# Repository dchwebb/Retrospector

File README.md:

# Retrospector

Retrospector is a Eurorack format stereo digital delay. 

Delay times can be set clocked or free-running and left and right channels can be independent or the right channel set as a multiple of the left channel. The delay times are switchable between short, long and reversed with maximum delay times over 5 minutes.

The feedback path can be filtered with settings allowing a sweep from low pass to high pass, or either separately. The delayed signal can be modulated for subtle chorussing effects or left and right channels fed back into each other to widen dual mono sources.

The feedback control allows greater than 100% regeneration allowing the delay to increase the volume of the delayed signal.

Three RGB LEDs display the delay times (using different colours to indicate clocking and channel linking) and the filter status (white to red with increasing low pass filtering and white to blue for high pass).

A USB port is available on the rear of the module providing configuration, debug and upgrade options via a serial interface.

# Technical
The module is constructed from a sandwich of three PCBs. The front panel is held to the control PCB using the potentiometers and jack sockets with light guides directing the RGB LEDs from the control PCB. The control PCB also houses the LED driver. All other components are on the component PCB and this is attached to the control PCB with standard 2.54mm headers. The component board is a 4 layer PCB; the others have 2 layers.

Retrospector is built around an STM32H743 microcontroller clocked at 400MHz. The MCU uses a pair of multi-channel 16-bit ADCs to digitise the stereo audio input signal and the various potentiometer and control voltage inputs.

The MCU controls the external DAC with I2S at 16 bits. The MCU's internal 12-bit DACs are used to control the linear VCA that carries out stereo mixing of the digital wet signal and analog dry signal.

Delay samples are held in external 32MB SDRAM controlled by the MCU's FMC peripheral. The MCU's internal memory is mainly used for DMA buffers and FIR filter buffers (better performance than the slower external RAM). The MCU also has both data and instruction caches which are used to greatly improve performance.

The three RGB LEDs are controlled by a Toshiba 9 channel LED driver (TB62781FNG) with the MCU setting colour and brightness over SPI and DMA.

The MCU also supports a USB micro-B port to allow upgrades, configuration and debugging via a serial console:

Annotated component PCB
-----------------------

A) A switched-mode power supply (Texas Instruments LM2675) converts the 12V rail to 5V which is then converted to 3.3V using an LDO. THe 5V rail also powers the RGB LEDs.

B) The mix control uses a 4 channel linear VCA (Alfa AS3364D) to control the Wet/Dry mix. This keeps the dry signal analog throughout.

C) The Output signals are mixed and inverted (to preserve signal polarity) with a TL074 and a TL072 op-amp.

D) The digital Wet signal is converted to analog using a Texas Instruments PCM5100 DAC.

E) The analog input signals (audio and control voltage) are scaled and mixed using a pair of MCP6004 op-amps.

F) The microcontroller is an STM32H743 running at 400MHz.

G) The delay beffers are stored in an external 32MB RAM module (ISSI IS42S16160J) allowing for over 5 minutes of stereo delay.

Errata
------
There were two errors on v2 hardware:

1. OpAmp U3 pin 2 and 3 incorrectly swapped. Bodge is to ground pin 3 of U3, remove capacitor C34, lift U3 pin 2 and connect it with a bodge wire to pad 2 of R24.
2. DRAM address line 12 was not connected. Bodge is to connect DRAM Pin 36 to MCU Pin 87.
3. Swapped C54 (tantalum 22uF) for ceramic 47uF (1206 25V X5R).

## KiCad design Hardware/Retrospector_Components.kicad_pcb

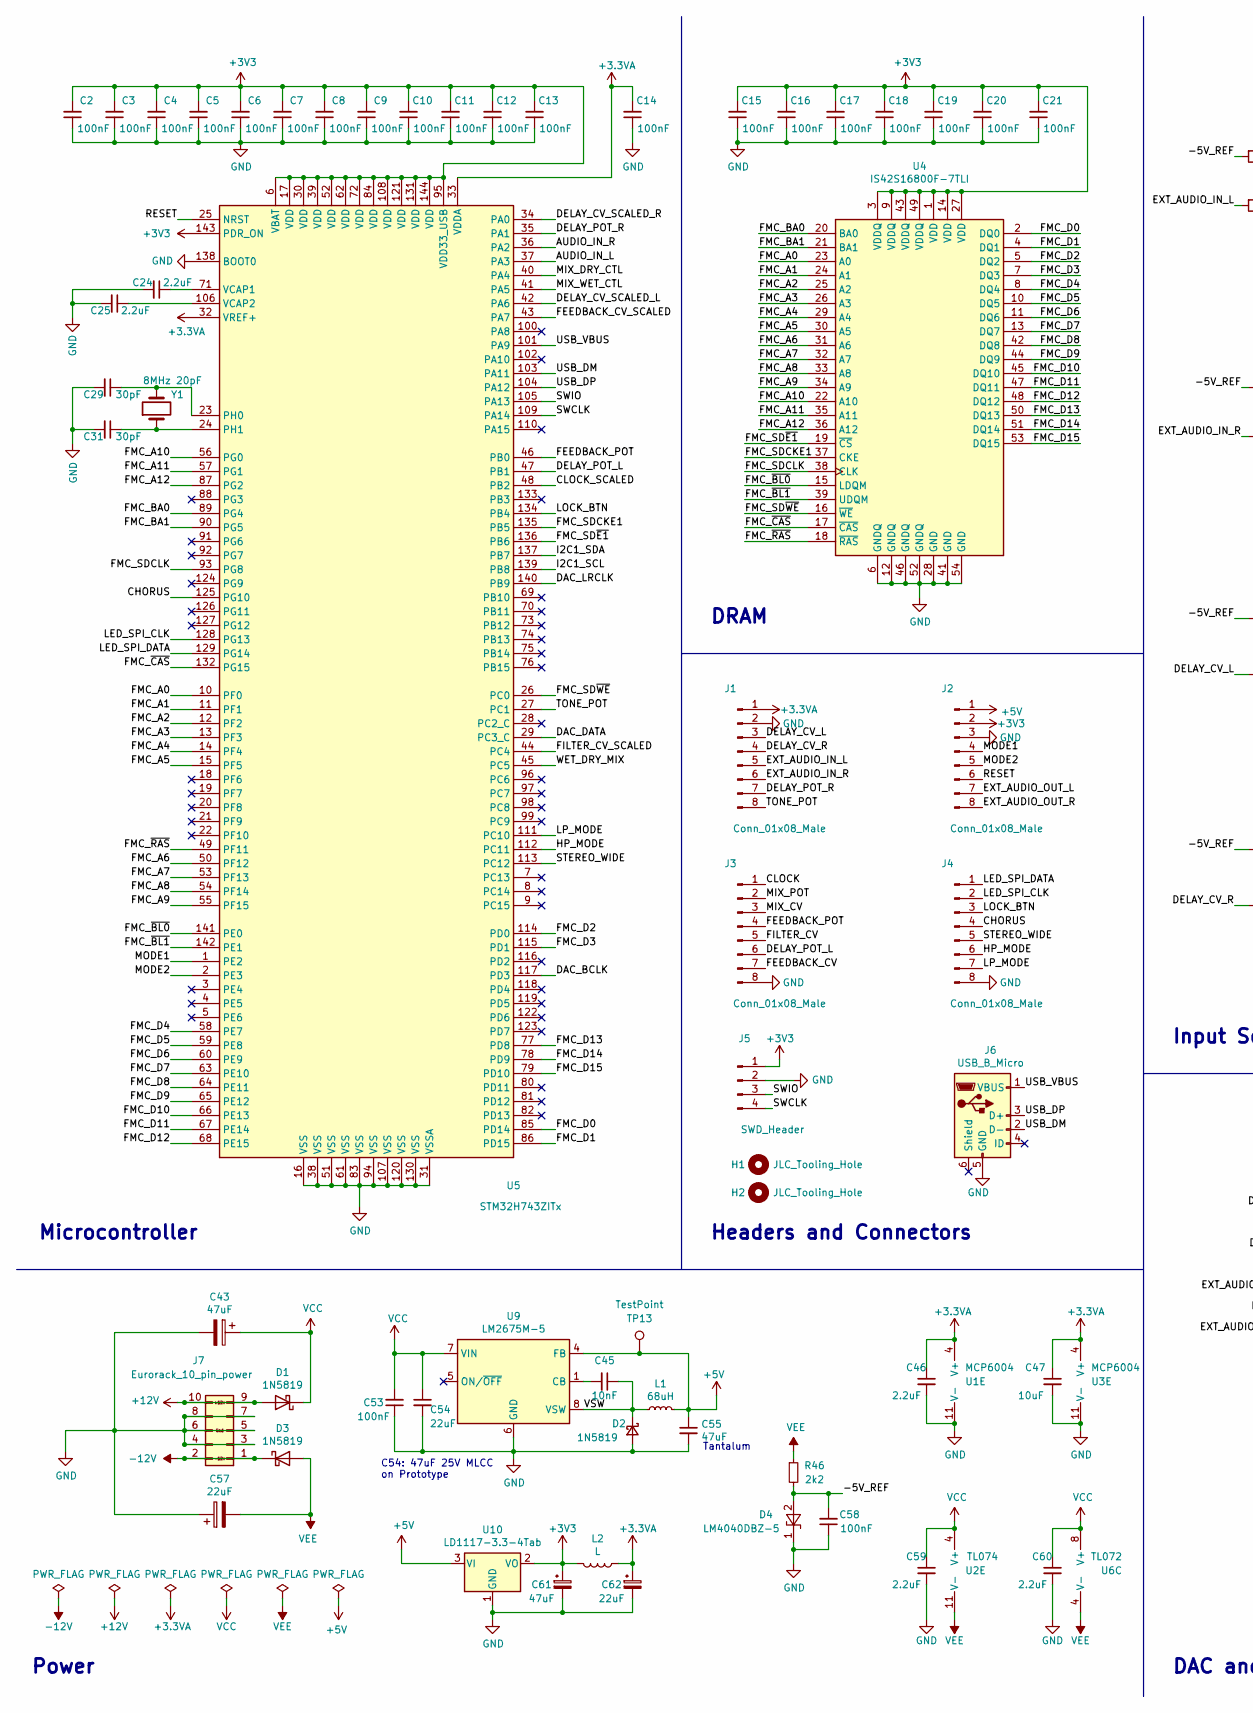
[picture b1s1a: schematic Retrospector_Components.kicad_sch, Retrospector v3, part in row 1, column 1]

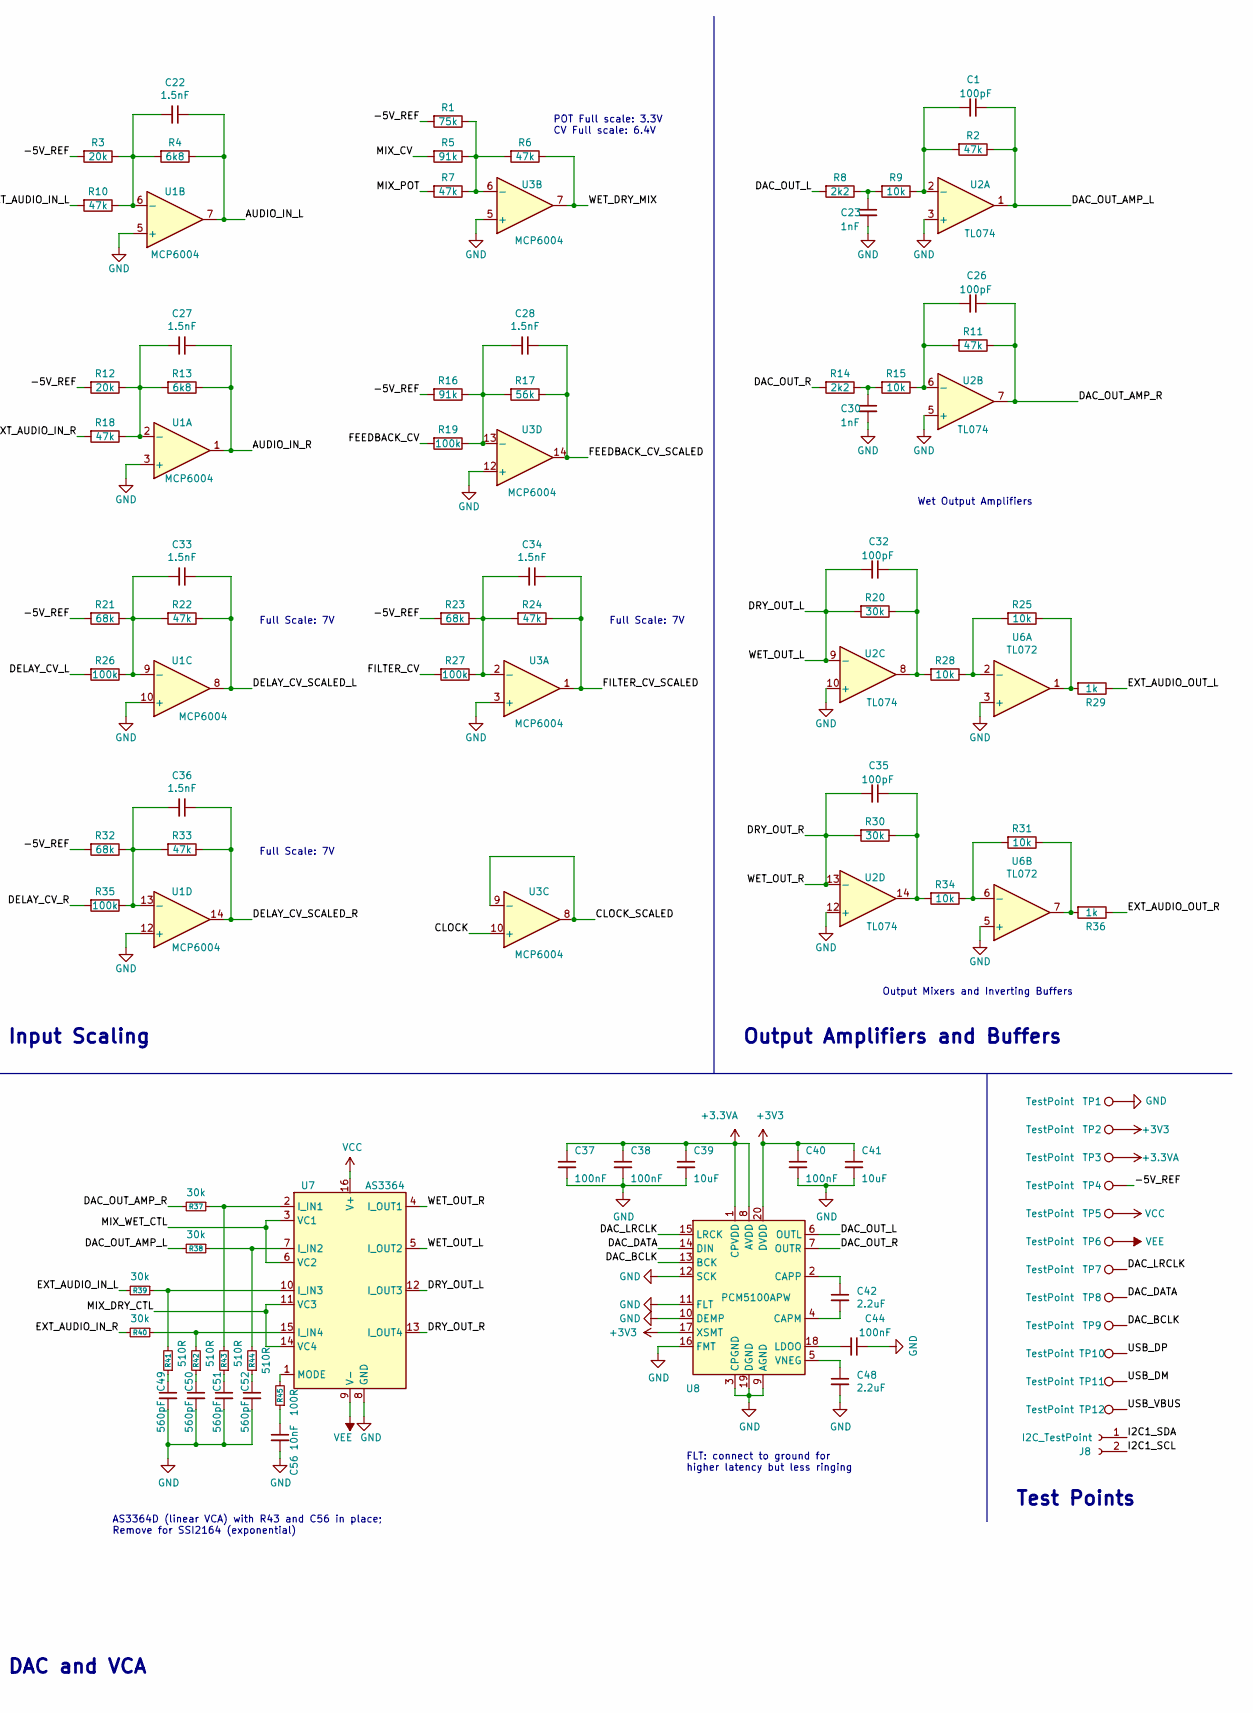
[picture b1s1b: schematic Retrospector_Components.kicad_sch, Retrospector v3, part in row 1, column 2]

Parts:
C1, C26, C32, C35: 100pF; C_0603_HandSoldering; Part_Number C14858
C2, C3, C4, C5, C6, C7, C8, C9, C10, C11, C12, C13, C14, C15, C16, C17, C18, C19, C20, C21, C37, C38, C40, C44, C58: 100nF; C_0603_HandSoldering; Part_Number C14663
C22, C27, C28, C33, C34, C36: 1.5nF; C_0603_HandSoldering; Part_Number C1595
C23, C30: 1nF; C_0603_HandSoldering; Part_Number C1588
C24, C25, C42, C46, C48, C59, C60: 2.2uF; C_0603_HandSoldering; Part_Number C23630
C29, C31: 30pF; C_0603_HandSoldering; Part_Number C22397
C39, C41, C47: 10uF; C_0805; Part_Number C15850
C43, C61: 47uF; CP_Elec_5x5.8; Part_Number C134798
C45, C56: 10nF; C_0603_HandSoldering; Part_Number C57112
C49, C50, C51, C52: 560pF; C_0603_HandSoldering; Part_Number C84721
C53: 100nF; C_0603_HandSoldering
C54: 22uF; C_1210
C55: 47uF; C_1210
C57, C62: 22uF; CP_Elec_4x5.8; Part_Number C134793
D1, D2, D3: 1N5819; D_SOD-123; Part_Number C8598
D4: LM4040DBZ-5; SOT-23; Part_Number C156291
H1, H2: JLC_Tooling_Hole; JLC_SMT_Tooling_Hole
J1, J2, J3, J4: Conn_01x08_Male; Pin_Header_Straight_1x08_Pitch2.54mm
J5: SWD_Header; SWD_header
J6: USB_B_Micro; USB_Micro-B_Amphenol
J7: Eurorack_10_pin_power; Eurorack_10_pin_header
J8: I2C_TestPoint; Pin_Header_Straight_1x02_Pitch2.54mm
L1: 68uH; TDK_Inductor_6.9x7.2
L2: L; L_0805_HandSoldering; Part_Number C1046
R1: 75k; R_0603_HandSoldering; Part_Number C23242
R2, R6, R7, R10, R11, R18, R22, R24, R33: 47k; R_0603_HandSoldering; Part_Number C25819
R3, R12: 20k; R_0603_HandSoldering; Part_Number C4184
R4, R13: 6k8; R_0603_HandSoldering; Part_Number C23212
R5, R16: 91k; R_0603_HandSoldering; Part_Number C23265
R8, R14, R46: 2k2; R_0603_HandSoldering; Part_Number C4190
R9, R15, R25, R28, R31, R34: 10k; R_0603_HandSoldering; Part_Number C25804
R17: 56k; R_0603_HandSoldering; Part_Number C23206
R19, R26, R27, R35: 100k; R_0603_HandSoldering; Part_Number C25803
R20, R30, R37, R38, R39, R40: 30k; R_0603_HandSoldering; Part_Number C22984
R21, R23, R32: 68k; R_0603_HandSoldering; Part_Number C23231
R29, R36: 1k; R_0603_HandSoldering; Part_Number C21190
R41, R42, R43, R44: 510R; R_0603_HandSoldering; Part_Number C23193
R45: 100R; R_0603_HandSoldering; Part_Number C22775
TP1, TP2, TP3, TP4, TP5, TP6: TestPoint; 1.3mm_Test_Point
TP7, TP8, TP9, TP10, TP11, TP12, TP13: TestPoint; Measurement_Point_Square-SMD-Pad_Small
U1, U3: MCP6004; SOIC-14_N; Part_Number C116668
U2: TL074; SOIC-14_N; Part_Number C6964
U4: IS42S16800F-7TLI; TSOP-II-54_22.2x10.16mm_P0.8mm; Part_Number C91278
U5: STM32H743ZITx; LQFP-144_20x20mm_P0.5mm; Part_Number C114408
U6: TL072; SOIC-8_3.9x4.9mm_Pitch1.27mm; Part_Number C6961
U7: AS3364; SOIC-16_3.9x9.9mm_Pitch1.27mm
U8: PCM5100APW; SSOP-20_4.4x6.5mm_Pitch0.65mm_Round_Pads; Part_Number C131154
U9: LM2675M-5; SOIC-8_3.9x4.9mm_Pitch1.27mm; Part_Number C180371
U10: LD1117-3.3-4Tab; SOT-223-3_TabPin2
Y1: 8MHz 20pF; Crystal_SMD_5032-2pin_5.0x3.2mm_HandSoldering; Part_Number C115962

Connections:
+3.3VA: C14.2, C37.1, C38.1, C39.1, C46.1, C47.1, C62.1, J1.1, L2.1, TP3.1, U1.4 (V+), U3.4 (V+), U5.32 (VREF+), U5.33 (VDDA), U8.1 (CPVDD), U8.8 (AVDD)
+3V3: C2.2, C3.2, C4.2, C5.2, C6.2, C7.2, C8.2, C9.2, C10.2, C11.2, C12.2, C13.2, C15.2, C16.2, C17.2, C18.2, C19.2, C20.2, C21.2, C40.1, C41.1, C61.1, J2.2, J5.1, L2.2, TP2.1, U4.1 (VDD), U4.3 (VDDQ), U4.9 (VDDQ), U4.14 (VDD), U4.27 (VDD), U4.43 (VDDQ), U4.49 (VDDQ), U5.6 (VBAT), U5.17 (VDD), U5.30 (VDD), U5.39 (VDD), U5.52 (VDD), U5.62 (VDD), U5.72 (VDD), U5.84 (VDD), U5.95 (VDD33_USB), U5.108 (VDD), U5.121 (VDD), U5.131 (VDD), U5.143 (PDR_ON), U5.144 (VDD), U8.17 (XSMT), U8.20 (DVDD), U10.2 (VO)
+5V: C55.1, J2.1, L1.2, TP13.1, U9.4 (FB), U10.3 (VI)
+12V: D1.2 (A), J7.9, J7.10
-12V: D3.1 (K), J7.1, J7.2
/-5V_REF: C58.2, D4.2 (A), R1.2, R3.2, R12.2, R16.2, R21.2, R23.2, R32.2, R46.2, TP4.1
/AUDIO_IN_L: C22.1, R4.1, U1.7, U5.37 (PA3)
/AUDIO_IN_R: C27.1, R13.1, U1.1, U5.36 (PA2)
/CHORUS: J4.4, U5.125 (PG10)
/CLOCK: J3.1, U3.10 (+)
/CLOCK_SCALED: U3.8, U3.9 (-), U5.48 (PB2)
/DAC_BCLK: TP9.1, U5.117 (PD3), U8.13 (BCK)
/DAC_DATA: TP8.1, U5.29 (PC3_C), U8.14 (DIN)
/DAC_LRCLK: TP7.1, U5.140 (PB9), U8.15 (LRCK)
/DAC_OUT_AMP_L: C1.1, R2.1, R38.2, U2.1
/DAC_OUT_AMP_R: C26.1, R11.1, R37.2, U2.7
/DAC_OUT_L: R8.2, U8.6 (OUTL)
/DAC_OUT_R: R14.2, U8.7 (OUTR)
/DELAY_CV_L: J1.3, R26.2
/DELAY_CV_R: J1.4, R35.2
/DELAY_CV_SCALED_L: C33.1, R22.1, U1.8, U5.42 (PA6)
/DELAY_CV_SCALED_R: C36.1, R33.1, U1.14, U5.34 (PA0)
/DELAY_POT_L: J3.6, U5.47 (PB1)
/DELAY_POT_R: J1.7, U5.35 (PA1)
/DRY_OUT_L: C32.2, R20.2, U2.9 (-), U7.5 (I_OUT2), U7.12 (I_OUT3)
/DRY_OUT_R: C35.2, R30.2, U2.13 (-), U7.4 (I_OUT1), U7.13 (I_OUT4)
/EXT_AUDIO_IN_L: J1.5, R10.2, R39.2
/EXT_AUDIO_IN_R: J1.6, R18.2, R40.2
/EXT_AUDIO_OUT_L: J2.7, R29.1
/EXT_AUDIO_OUT_R: J2.8, R36.1
/FEEDBACK_CV: J3.7, R19.2
/FEEDBACK_CV_SCALED: C28.1, R17.1, U3.14, U5.43 (PA7)
/FEEDBACK_POT: J3.4, U5.46 (PB0)
/FILTER_CV: J3.5, R27.2
/FILTER_CV_SCALED: C34.1, R24.1, U3.1, U5.44 (PC4)
/FMC_A0: U4.23 (A0), U5.10 (PF0)
/FMC_A1: U4.24 (A1), U5.11 (PF1)
/FMC_A2: U4.25 (A2), U5.12 (PF2)
/FMC_A3: U4.26 (A3), U5.13 (PF3)
/FMC_A4: U4.29 (A4), U5.14 (PF4)
/FMC_A5: U4.30 (A5), U5.15 (PF5)
/FMC_A6: U4.31 (A6), U5.50 (PF12)
/FMC_A7: U4.32 (A7), U5.53 (PF13)
/FMC_A8: U4.33 (A8), U5.54 (PF14)
/FMC_A9: U4.34 (A9), U5.55 (PF15)
/FMC_A10: U4.22 (A10), U5.56 (PG0)
/FMC_A11: U4.35 (A11), U5.57 (PG1)
/FMC_A12: U4.36 (A12), U5.87 (PG2)
/FMC_BA0: U4.20 (BA0), U5.89 (PG4)
/FMC_BA1: U4.21 (BA1), U5.90 (PG5)
/FMC_D0: U4.2 (DQ0), U5.85 (PD14)
/FMC_D1: U4.4 (DQ1), U5.86 (PD15)
/FMC_D2: U4.5 (DQ2), U5.114 (PD0)
/FMC_D3: U4.7 (DQ3), U5.115 (PD1)
/FMC_D4: U4.8 (DQ4), U5.58 (PE7)
/FMC_D5: U4.10 (DQ5), U5.59 (PE8)
/FMC_D6: U4.11 (DQ6), U5.60 (PE9)
/FMC_D7: U4.13 (DQ7), U5.63 (PE10)
/FMC_D8: U4.42 (DQ8), U5.64 (PE11)
/FMC_D9: U4.44 (DQ9), U5.65 (PE12)
/FMC_D10: U4.45 (DQ10), U5.66 (PE13)
/FMC_D11: U4.47 (DQ11), U5.67 (PE14)
/FMC_D12: U4.48 (DQ12), U5.68 (PE15)
/FMC_D13: U4.50 (DQ13), U5.77 (PD8)
/FMC_D14: U4.51 (DQ14), U5.78 (PD9)
/FMC_D15: U4.53 (DQ15), U5.79 (PD10)
/FMC_SDCKE1: U4.37 (CKE), U5.135 (PB5)
/FMC_SDCLK: U4.38 (CLK), U5.93 (PG8)
/FMC_SD~E1: U4.19 (~CS), U5.136 (PB6)
/FMC_SD~WE: U4.16 (~WE), U5.26 (PC0)
/FMC_~BL0: U4.15 (LDQM), U5.141 (PE0)
/FMC_~BL1: U4.39 (UDQM), U5.142 (PE1)
/FMC_~CAS: U4.17 (~CAS), U5.132 (PG15)
/FMC_~RAS: U4.18 (~RAS), U5.49 (PF11)
/HP_MODE: J4.6, U5.112 (PC11)
/I2C1_SCL: J8.2, U5.139 (PB8)
/I2C1_SDA: J8.1, U5.137 (PB7)
/LED_SPI_CLK: J4.2, U5.128 (PG13)
/LED_SPI_DATA: J4.1, U5.129 (PG14)
/LOCK_BTN: J4.3, U5.134 (PB4)
/LP_MODE: J4.7, U5.111 (PC10)
/MIX_CV: J3.3, R5.2
/MIX_DRY_CTL: U5.40 (PA4), U7.11 (VC3), U7.14 (VC4)
/MIX_POT: J3.2, R7.2
/MIX_WET_CTL: U5.41 (PA5), U7.3 (VC1), U7.6 (VC2)
/MODE1: J2.4, U5.1 (PE2)
/MODE2: J2.5, U5.2 (PE3)
/RESET: J2.6, U5.25 (NRST)
/STEREO_WIDE: J4.5, U5.113 (PC12)
/SWCLK: J5.4, U5.109 (PA14)
/SWIO: J5.3, U5.105 (PA13)
/TONE_POT: J1.8, U5.27 (PC1)
/USB_DM: J6.2 (D-), TP11.1, U5.103 (PA11)
/USB_DP: J6.3 (D+), TP10.1, U5.104 (PA12)
/USB_VBUS: J6.1 (VBUS), TP12.1, U5.101 (PA9)
/VSW: C45.1, D2.1 (K), L1.1, U9.8 (VSW)
/WET_DRY_MIX: R6.1, U3.7, U5.45 (PC5)
GND: C2.1, C3.1, C4.1, C5.1, C6.1, C7.1, C8.1, C9.1, C10.1, C11.1, C12.1, C13.1, C14.1, C15.1, C16.1, C17.1, C18.1, C19.1, C20.1, C21.1, C23.2, C24.2, C25.2, C29.2, C30.2, C31.2, C37.2, C38.2, C39.2, C40.2, C41.2, C43.2, C44.1, C46.2, C47.2, C48.2, C49.2, C50.2, C51.2, C52.2, C53.1, C54.2, C55.2, C56.2, C57.1, C58.1, C59.2, C60.2, C61.2, C62.2, D2.2 (A), D4.1 (K), J1.2, J2.3, J3.8, J4.8, J5.2, J6.5 (GND), J7.3, J7.4, J7.5, J7.6, J7.7, J7.8, TP1.1, U1.3 (+), U1.5 (+), U1.10 (+), U1.11 (V-), U1.12 (+), U2.3 (+), U2.5 (+), U2.10 (+), U2.12 (+), U3.3 (+), U3.5 (+), U3.11 (V-), U3.12 (+), U4.6 (GNDQ), U4.12 (GNDQ), U4.28 (GND), U4.41 (GND), U4.46 (GNDQ), U4.52 (GNDQ), U4.54 (GND), U5.16 (VSS), U5.31 (VSSA), U5.38 (VSS), U5.51 (VSS), U5.61 (VSS), U5.83 (VSS), U5.94 (VSS), U5.107 (VSS), U5.120 (VSS), U5.130 (VSS), U5.138 (BOOT0), U6.3 (+), U6.5 (+), U7.8 (GND), U8.3 (CPGND), U8.9 (AGND), U8.10 (DEMP), U8.11 (FLT), U8.12 (SCK), U8.16 (FMT), U8.19 (DGND), U9.6 (GND), U10.1 (GND)
unnamed: C1.2, R2.2, R9.1, U2.2 (-)
unnamed: C22.2, R3.1, R4.2, R10.1, U1.6 (-)
unnamed: C23.1, R8.1, R9.2
unnamed: C24.1, U5.71 (VCAP1)
unnamed: C25.1, U5.106 (VCAP2)
unnamed: C26.2, R11.2, R15.1, U2.6 (-)
unnamed: C27.2, R12.1, R13.2, R18.1, U1.2 (-)
unnamed: C28.2, R16.1, R17.2, R19.1, U3.13 (-)
unnamed: C29.1, U5.23 (PH0), Y1.2
unnamed: C30.1, R14.1, R15.2
unnamed: C31.1, U5.24 (PH1), Y1.1
unnamed: C32.1, R20.1, R28.2, U2.8
unnamed: C33.2, R21.1, R22.2, R26.1, U1.9 (-)
unnamed: C34.2, R23.1, R24.2, R27.1, U3.2 (-)
unnamed: C35.1, R30.1, R34.2, U2.14
unnamed: C36.2, R32.1, R33.2, R35.1, U1.13 (-)
unnamed: C42.1, U8.2 (CAPP)
unnamed: C42.2, U8.4 (CAPM)
unnamed: C44.2, U8.18 (LDOO)
unnamed: C45.2, U9.1 (CB)
unnamed: C48.1, U8.5 (VNEG)
unnamed: C49.1, R41.1
unnamed: C50.1, R42.1
unnamed: C51.1, R43.1
unnamed: C52.1, R44.1
unnamed: C56.1, R45.1
unnamed: R1.1, R5.1, R6.2, R7.1, U3.6 (-)
unnamed: R25.1, R29.2, U6.1
unnamed: R25.2, R28.1, U6.2 (-)
unnamed: R31.1, R36.2, U6.7
unnamed: R31.2, R34.1, U6.6 (-)
unnamed: R37.1, R43.2, U7.2 (I_IN1)
unnamed: R38.1, R44.2, U7.7 (I_IN2)
unnamed: R39.1, R41.2, U7.10 (I_IN3)
unnamed: R40.1, R42.2, U7.15 (I_IN4)
unnamed: R45.2, U7.1 (MODE)
VCC: C43.1, C53.2, C54.1, C59.1, C60.1, D1.1 (K), TP5.1, U2.4 (V+), U6.8 (V+), U7.16 (V+), U9.7 (VIN)
VEE: C57.2, D3.2 (A), R46.1, TP6.1, U2.11 (V-), U6.4 (V-), U7.9 (V-)

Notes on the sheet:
DRAM
C54: 47uF 25V MLCC on Prototype
Input Scaling
Full Scale: 7V
Microcontroller
Headers and Connectors
Wet Output Amplifiers
POT Full scale: 3.3V CV Full scale: 6.4V
Tantalum
Power
AS3364D (linear VCA) with R43 and C56 in place; Remove for SSI2164 (exponential)
DAC and VCA
Output Mixers and Inverting Buffers
Output Amplifiers and Buffers
FLT: connect to ground for higher latency but less ringing
Test Points

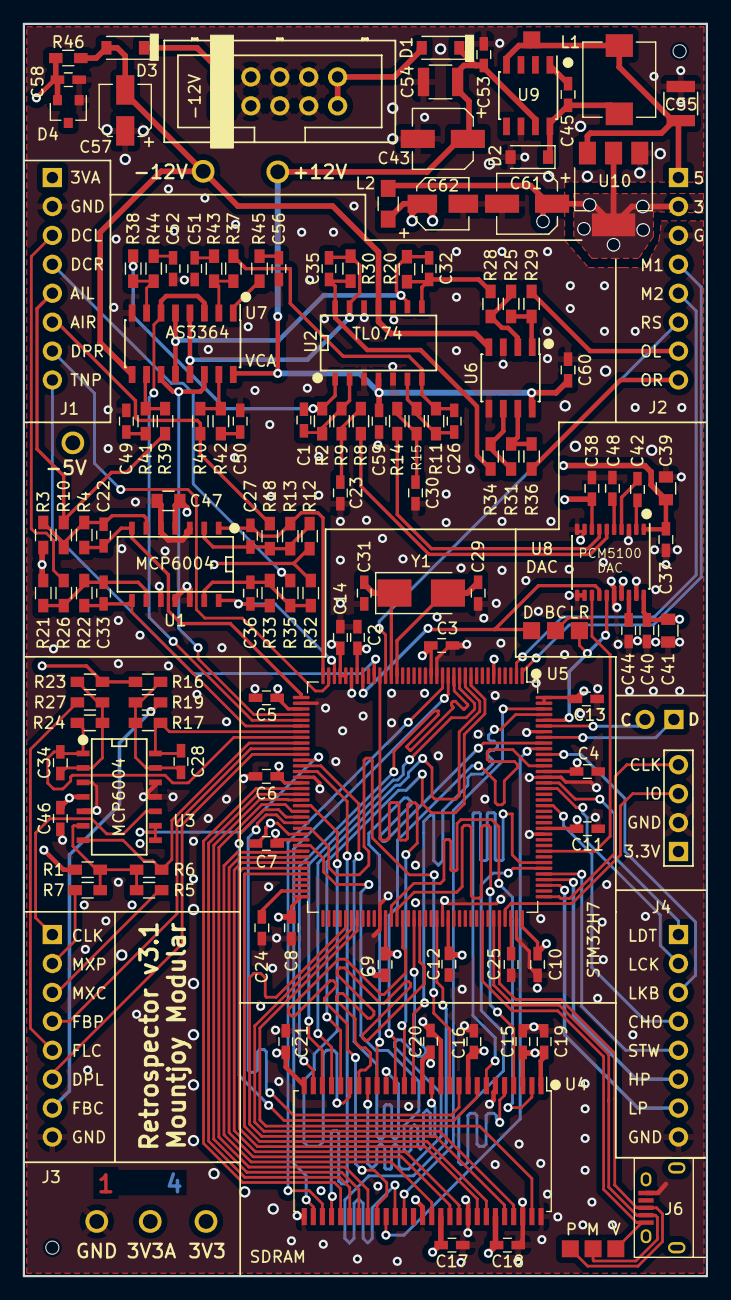
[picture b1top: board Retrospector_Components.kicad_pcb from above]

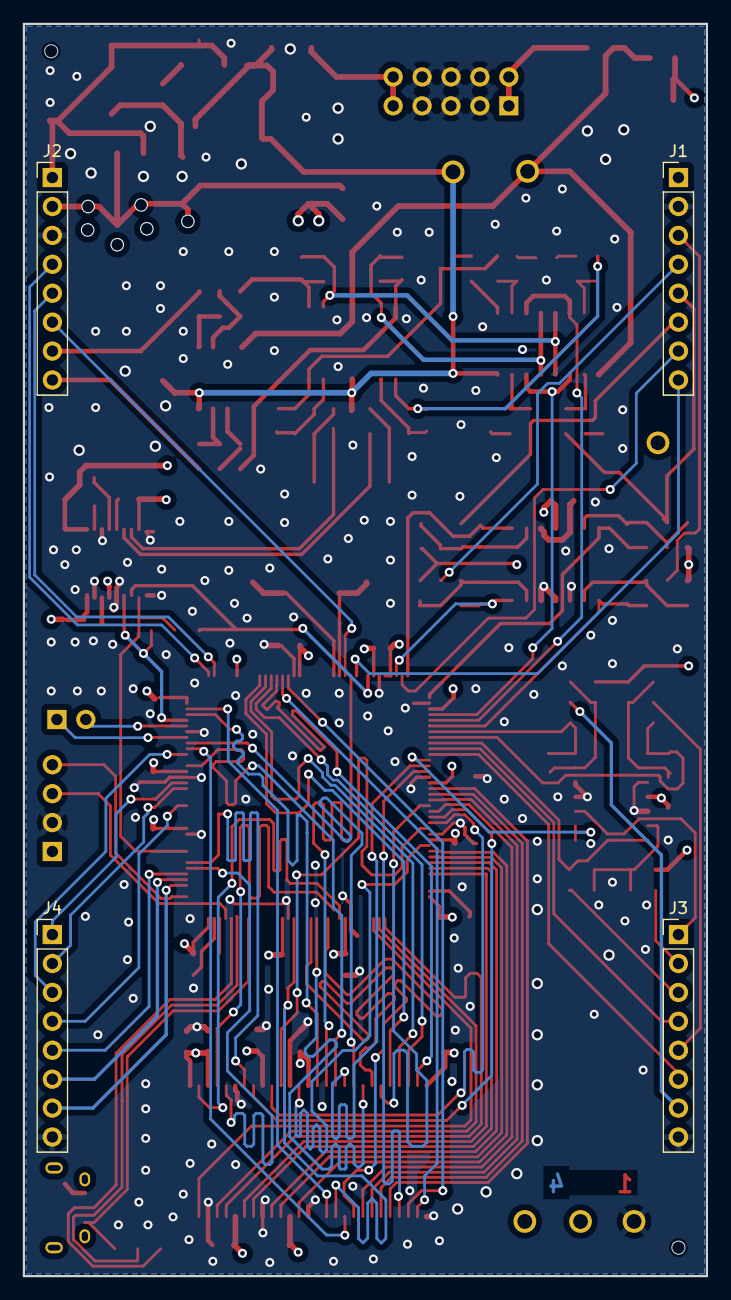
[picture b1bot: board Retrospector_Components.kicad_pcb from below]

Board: 4 copper layers, 60.0 x 110.0 mm, 149 parts (4 on the bottom side), 136 nets.

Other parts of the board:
4_Layer_Marker: 4_Layer_Markers

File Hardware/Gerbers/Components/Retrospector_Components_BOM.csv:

"Comment","Designator","Footprint","LCSC Part #"
"100pF","C1, C26, C32, C35, ","C_0603_HandSoldering","C14858"
"100nF","C2, C3, C4, C5, C6, C7, C8, C9, C10, C11, C12, C13, C14, C15, C16, C17, C18, C19, C20, C21, C37, C38, C40, C44, C53, C58, ","C_0603_HandSoldering","C14663"
"1.5nF","C22, C27, C28, C33, C34, C36, ","C_0603_HandSoldering","C1595"
"1nF","C23, C30, ","C_0603_HandSoldering","C1588"
"2.2uF","C24, C25, C42, C46, C48, C59, C60, ","C_0603_HandSoldering","C23630"
"30pF","C29, C31, ","C_0603_HandSoldering","C22397"
"10uF","C39, C41, C47, ","C_0805","C15850 "
"47uF","C43, C61, ","CP_Elec_5x5.8","C134798"
"10nF","C45, C56, ","C_0603_HandSoldering","C57112"
"560pF","C49, C50, C51, C52, ","C_0603_HandSoldering","C84721"
"22uF","C57, C62, ","CP_Elec_4x5.8","C134793"
"1N5819","D1, D2, D3, ","D_SOD-123","C8598"
"LM4040DBZ-5","D4, ","SOT-23","C156291"
"L","L2, ","L_0805_HandSoldering","C1046"
"75k","R1, ","R_0603_HandSoldering","C23242 "
"47k","R2, R6, R7, R10, R11, R18, R22, R24, R33, ","R_0603_HandSoldering","C25819"
"20k","R3, R12, ","R_0603_HandSoldering","C4184 "
"6k8","R4, R13, ","R_0603_HandSoldering","C23212 "
"91k","R5, R16, ","R_0603_HandSoldering","C23265"
"2k2","R8, R14, R46, ","R_0603_HandSoldering","C4190"
"10k","R9, R15, R25, R28, R31, R34, ","R_0603_HandSoldering","C25804"
"56k","R17, ","R_0603_HandSoldering","C23206"
"100k","R19, R26, R27, R35, ","R_0603_HandSoldering","C25803"
"30k","R20, R30, R37, R38, R39, R40, ","R_0603_HandSoldering","C22984"
"68k","R21, R23, R32, ","R_0603_HandSoldering","C23231"
"1k","R29, R36, ","R_0603_HandSoldering","C21190"
"510R","R41, R42, R43, R44, ","R_0603_HandSoldering","C23193"
"100R","R45, ","R_0603_HandSoldering","C22775"
"MCP6004","U1, U3, ","SOIC-14_N","C116668"
"TL074","U2, ","SOIC-14_N","C6964"
"IS42S16800F-7TLI","U4, ","TSOP-II-54_22.2x10.16mm_P0.8mm","C91278"
"STM32H743ZITx","U5, ","LQFP-144_20x20mm_P0.5mm","C114408"
"TL072","U6, ","SOIC-8_3.9x4.9mm_Pitch1.27mm","C6961"
"PCM5100APW","U8, ","SSOP-20_4.4x6.5mm_Pitch0.65mm_Round_Pads","C131154"
"LM2675M-5","U9, ","SOIC-8_3.9x4.9mm_Pitch1.27mm","C180371"
"8MHz 20pF","Y1, ","Crystal_SMD_5032-2pin_5.0x3.2mm_HandSoldering","C115962"

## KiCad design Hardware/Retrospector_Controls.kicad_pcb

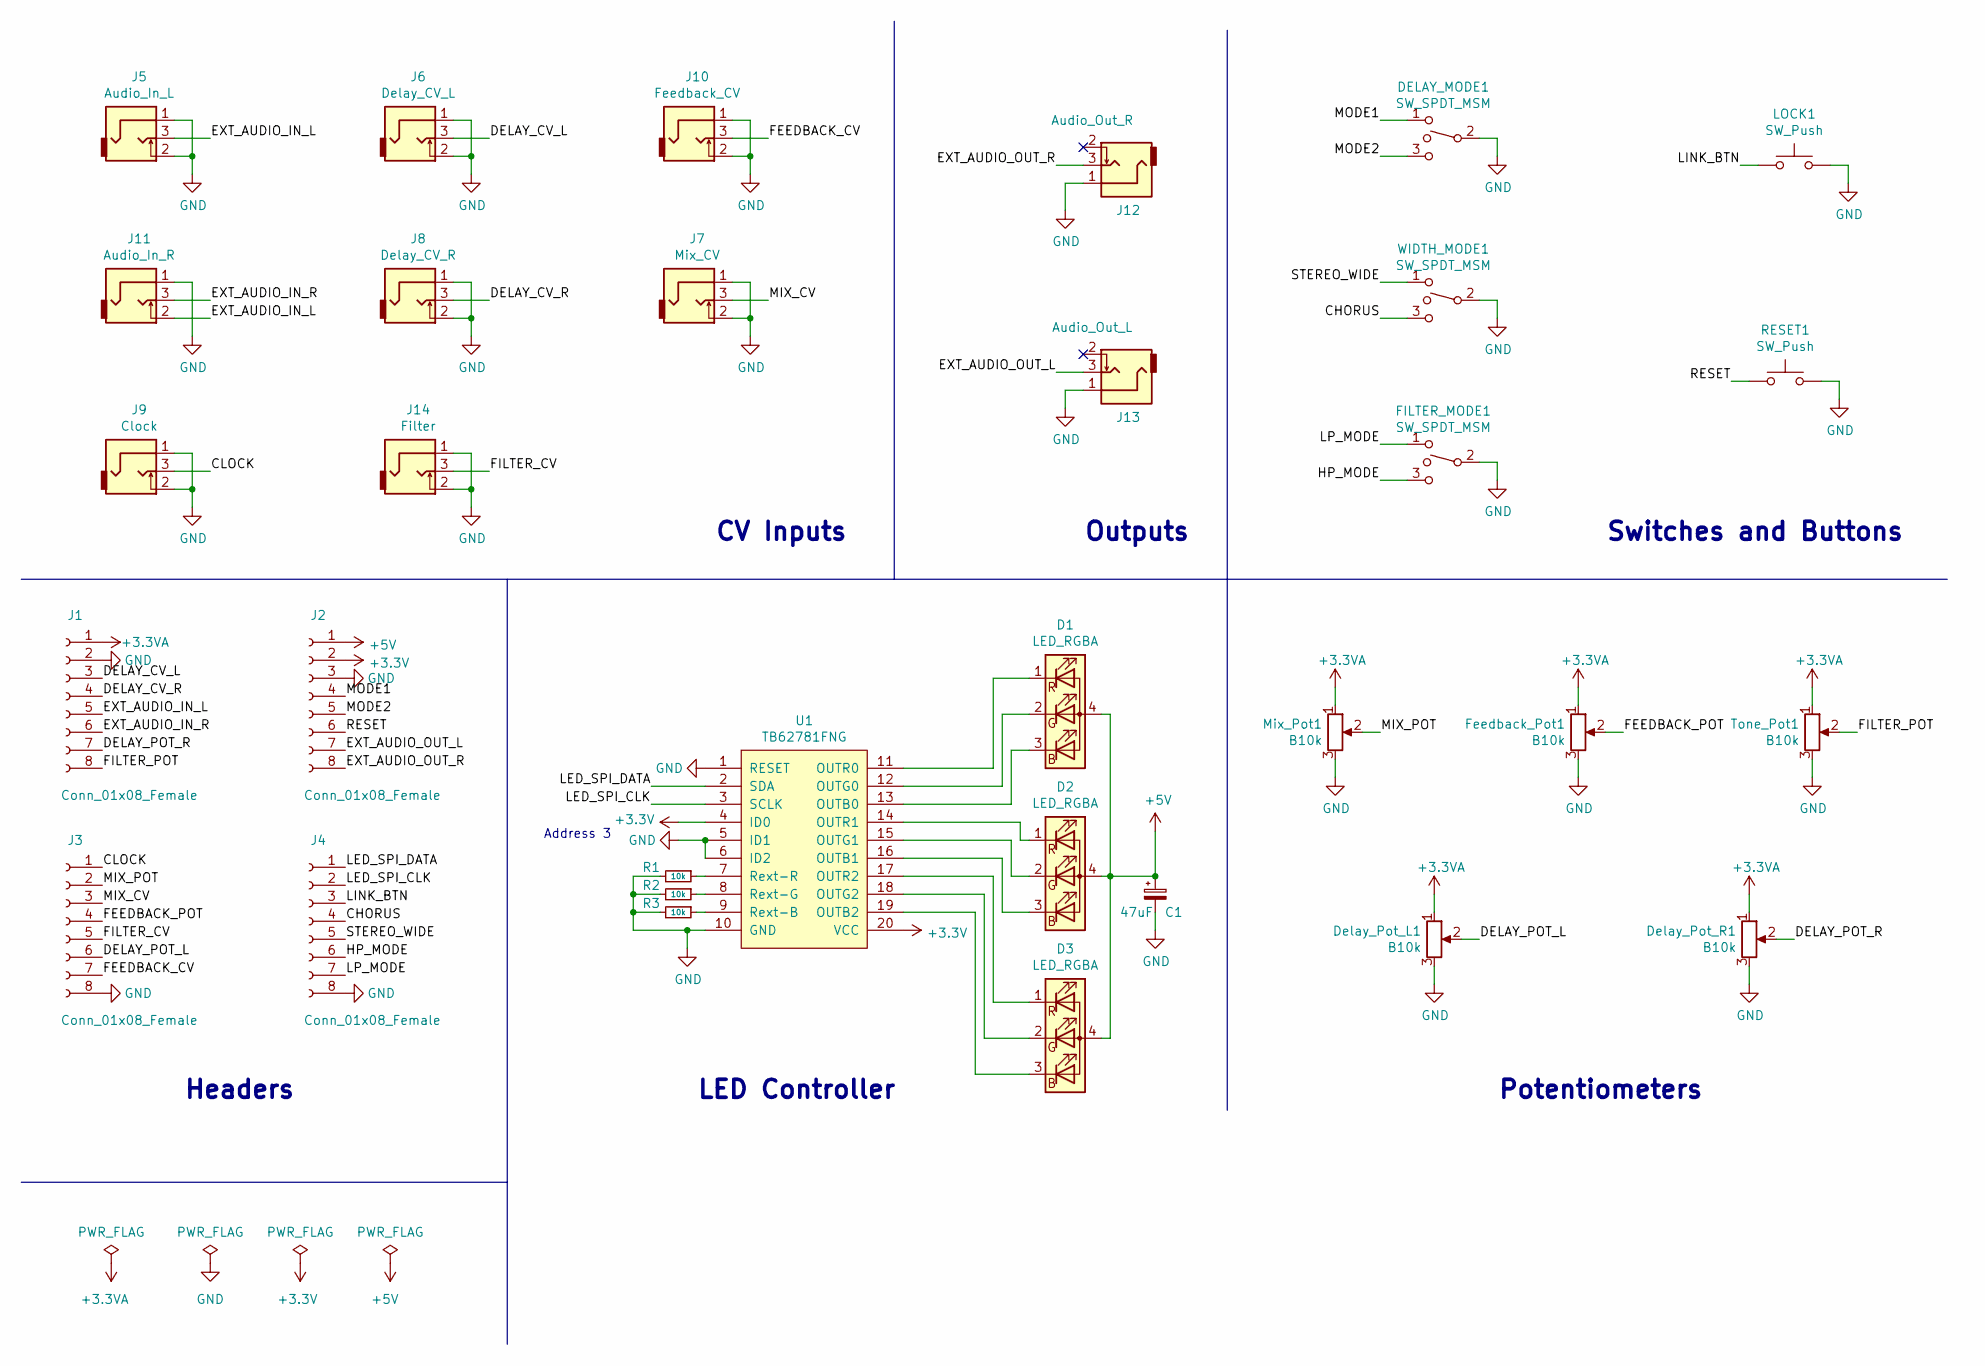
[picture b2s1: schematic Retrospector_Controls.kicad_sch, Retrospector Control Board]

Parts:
C1: 47uF; CP_Elec_5x5.8
D1, D2, D3: LED_RGBA; LED_RGB_PLCC4
DELAY_MODE1: SW_SPDT_MSM; SPDT_SubMiniature_Aligned
Delay_Pot_L1: B10k; Alpha_9mm_Potentiometer_Aligned
Delay_Pot_R1: B10k; Alpha_9mm_Potentiometer_Aligned
FILTER_MODE1: SW_SPDT_MSM; SPDT_SubMiniature_Aligned
Feedback_Pot1: B10k; Alpha_9mm_Potentiometer_Aligned
J1, J2, J3, J4: Conn_01x08_Female; Socket_Strip_Straight_1x08_Pitch2.54mm
J5: Audio_In_L; THONKICONN_hole
J6: Delay_CV_L; THONKICONN_hole
J7: Mix_CV; THONKICONN_hole
J8: Delay_CV_R; THONKICONN_hole
J9: Clock; THONKICONN_hole
J10: Feedback_CV; THONKICONN_hole
J11: Audio_In_R; THONKICONN_hole
J12: Audio_Out_R; THONKICONN_hole
J13: Audio_Out_L; THONKICONN_hole
J14: Filter; THONKICONN_hole
LOCK1: SW_Push; SW_PUSH_6mm_aligned
Mix_Pot1: B10k; Alpha_9mm_Potentiometer_Aligned
R1, R2, R3: 10k; R_0603_HandSoldering
RESET1: SW_Push; SW_PUSH_6mm_aligned
Tone_Pot1: B10k; Alpha_9mm_Potentiometer_Aligned
U1: TB62781FNG; SSOP-20_4.4x6.5mm_Pitch0.65mm
WIDTH_MODE1: SW_SPDT_MSM; SPDT_SubMiniature_Aligned

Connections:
+3.3VA: Delay_Pot_L1.1, Delay_Pot_R1.1, Feedback_Pot1.1, J1.1, Mix_Pot1.1, Tone_Pot1.1
+3V3: J2.2, U1.4 (ID0), U1.20 (VCC)
+5V: C1.1, D1.4 (A), D2.4 (A), D3.4 (A), J2.1
/CHORUS: J4.5, WIDTH_MODE1.1
/CLOCK: J3.1, J9.3
/DELAY_CV_L: J1.3, J6.3
/DELAY_CV_R: J1.4, J8.3
/DELAY_POT_L: Delay_Pot_L1.2, J3.6
/DELAY_POT_R: Delay_Pot_R1.2, J1.7
/EXT_AUDIO_IN_L: J1.5, J5.3, J11.2
/EXT_AUDIO_IN_R: J1.6, J11.3
/EXT_AUDIO_OUT_L: J2.7, J13.3
/EXT_AUDIO_OUT_R: J2.8, J12.3
/FEEDBACK_CV: J3.7, J10.3
/FEEDBACK_POT: Feedback_Pot1.2, J3.4
/FILTER_CV: J3.5, J14.3
/FILTER_POT: J1.8, Tone_Pot1.2
/HP_MODE: FILTER_MODE1.3, J4.6
/LED_SPI_CLK: J4.2, U1.3 (SCLK)
/LED_SPI_DATA: J4.1, U1.2 (SDA)
/LINK_BTN: J4.3, LOCK1.1
/LP_MODE: FILTER_MODE1.1, J4.7
/MIX_CV: J3.3, J7.3
/MIX_POT: J3.2, Mix_Pot1.2
/MODE1: DELAY_MODE1.1, J2.4
/MODE2: DELAY_MODE1.3, J2.5
/PINGPONG: J4.4, WIDTH_MODE1.3
/RESET: J2.6, RESET1.1
GND: C1.2, DELAY_MODE1.2, Delay_Pot_L1.3, Delay_Pot_R1.3, FILTER_MODE1.2, Feedback_Pot1.3, J1.2, J2.3, J3.8, J4.8, J5.1, J5.2, J6.1, J6.2, J7.1, J7.2, J8.1, J8.2, J9.1, J9.2, J10.1, J10.2, J11.1, J12.1, J13.1, J14.1, J14.2, LOCK1.2, Mix_Pot1.3, R1.2, R2.2, R3.2, RESET1.2, Tone_Pot1.3, U1.1 (RESET), U1.5 (ID1), U1.6 (ID2), U1.10 (GND), WIDTH_MODE1.2
unnamed: D1.1 (RK), U1.11 (OUTR0)
unnamed: D1.2 (GK), U1.12 (OUTG0)
unnamed: D1.3 (BK), U1.13 (OUTB0)
unnamed: D2.1 (RK), U1.14 (OUTR1)
unnamed: D2.2 (GK), U1.15 (OUTG1)
unnamed: D2.3 (BK), U1.16 (OUTB1)
unnamed: D3.1 (RK), U1.17 (OUTR2)
unnamed: D3.2 (GK), U1.18 (OUTG2)
unnamed: D3.3 (BK), U1.19 (OUTB2)
unnamed: R1.1, U1.7 (Rext-R)
unnamed: R2.1, U1.8 (Rext-G)
unnamed: R3.1, U1.9 (Rext-B)

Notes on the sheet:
Potentiometers
Address 3
LED Controller
Switches and Buttons
CV Inputs
Outputs
Headers

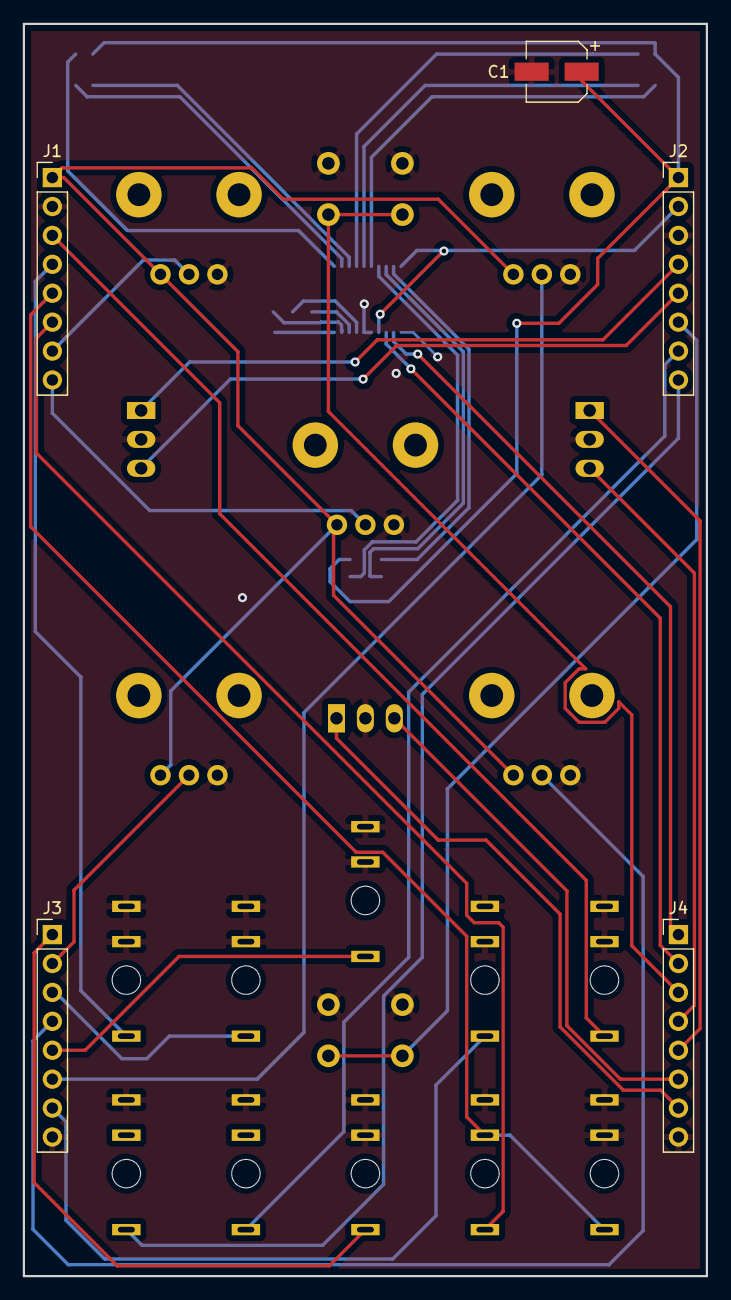
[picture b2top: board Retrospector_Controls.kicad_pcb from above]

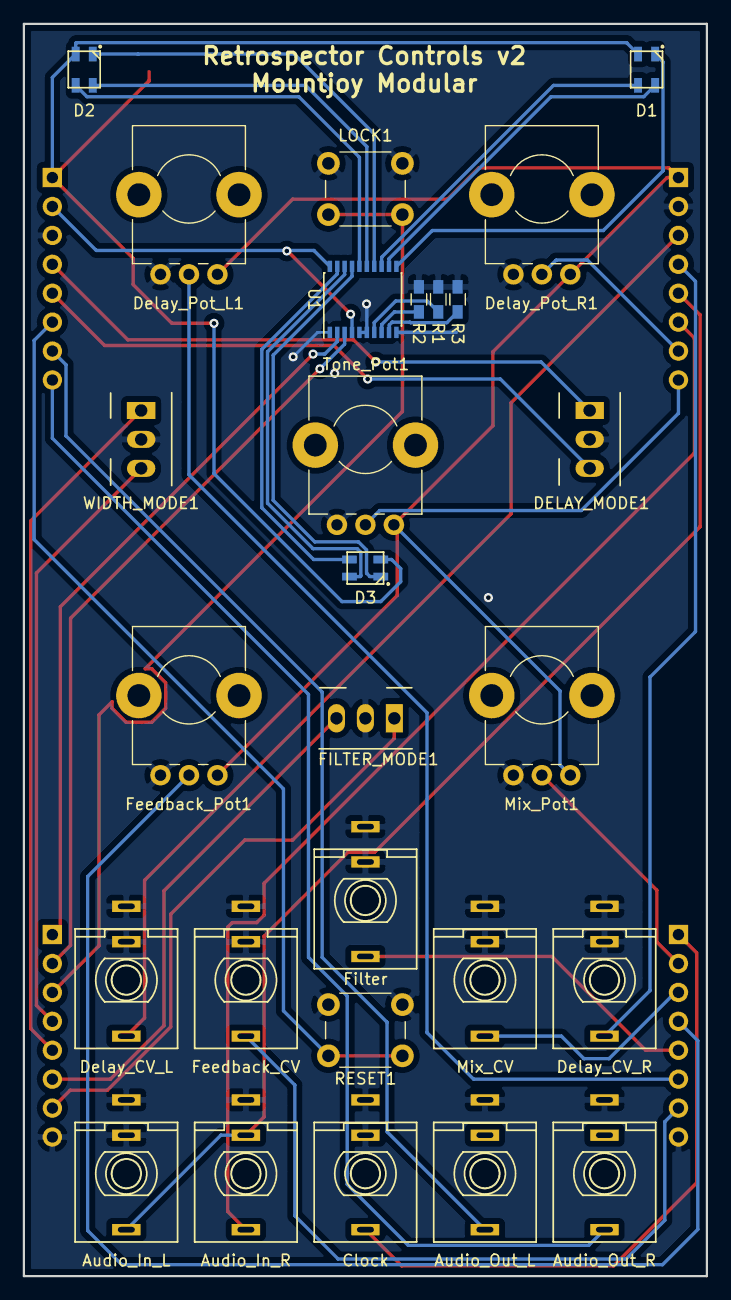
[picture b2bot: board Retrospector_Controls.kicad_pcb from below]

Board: 2 copper layers, 60.0 x 110.0 mm, 32 parts (27 on the bottom side), 41 nets.

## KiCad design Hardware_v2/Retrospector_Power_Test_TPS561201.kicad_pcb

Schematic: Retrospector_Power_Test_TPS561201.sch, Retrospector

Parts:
C1, C2, C5: 10uF; R_0805; Part_Number C57112
C3: 100nF; R_0805; Part_Number C57112
C4: 47uF; R_1206; Part_Number C57112
C41: 22uF; CP_Elec_4x5.8; Part_Number C178597
D3: 1N5819; D_SOD-123; Part_Number C8598
J2: Eurorack_10_pin_power; Eurorack_10_pin_header
JP1, JP3: Jumper_Closed; R_1206
JP2, JP4: Jumper_Open; R_1206
L1: L; L_0805_HandSoldering; Part_Number C1046
L3: 4.7uH; L_0806; Part_Number C326343
R1: 56k; R_0603_HandSoldering
R2: 10k; R_0603_HandSoldering
TP1, TP2, TP3, TP5: TestPoint; 1.3mm_Test_Point
U1: TPS561201; SOT-23-6_Handsoldering
U2: LD1117-3.3-4Tab; SOT-223-3_TabPin2

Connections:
+3.3VA: L1.1, TP3.1
+3V3: JP3.1 (A), JP4.1 (A), TP2.1
+12V: D3.2 (A), J2.9, J2.10
-12V: J2.1, J2.2
/CB: C3.2, U1.6
/FB: R1.2, R2.1, U1.4
/VIN: C5.1, JP1.2 (B), JP2.1 (A), U2.3 (VI)
/VOUT: C41.1, JP4.2 (B), L1.2, U2.2 (VO)
/VSW: C3.1, L3.1, U1.2
/V_Int: C4.1, JP2.2 (B), JP3.2 (B), L3.2, R1.1
GND: C1.2, C2.2, C4.2, C5.2, C41.2, J2.3, J2.4, J2.5, J2.6, J2.7, J2.8, R2.2, TP1.1, U1.1, U2.1 (GND)
VCC: C1.1, C2.1, D3.1 (K), JP1.1 (A), TP5.1, U1.3

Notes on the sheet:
Power
Test Points
R1 R2 L3 C2 C4 Ripple Switching
TPS561201
3.3V 33.2k 10k 3.3uH 10uF+10uF 47uF 19mV 425.46 kHz
5V 56.2k 10k 4.7uH 10uF+10uF 47uF 18mV 496.87kHz
Vout = 0.768 x (1 + R1/R2) 0.768 * (1 + 56/10) = 5.069 0.768 * (1 + 33/10) = 3.302

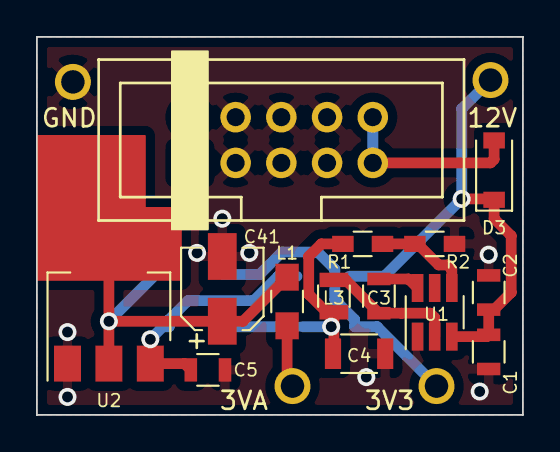
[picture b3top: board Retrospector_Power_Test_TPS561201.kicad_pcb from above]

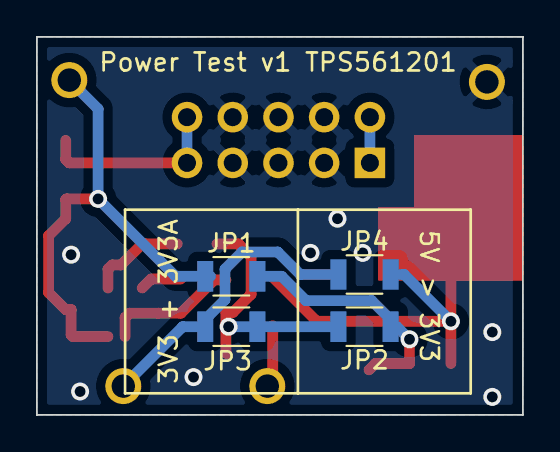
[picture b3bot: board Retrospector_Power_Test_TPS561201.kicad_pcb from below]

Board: 2 copper layers, 27.0 x 21.0 mm, 22 parts (4 on the bottom side), 12 nets.
